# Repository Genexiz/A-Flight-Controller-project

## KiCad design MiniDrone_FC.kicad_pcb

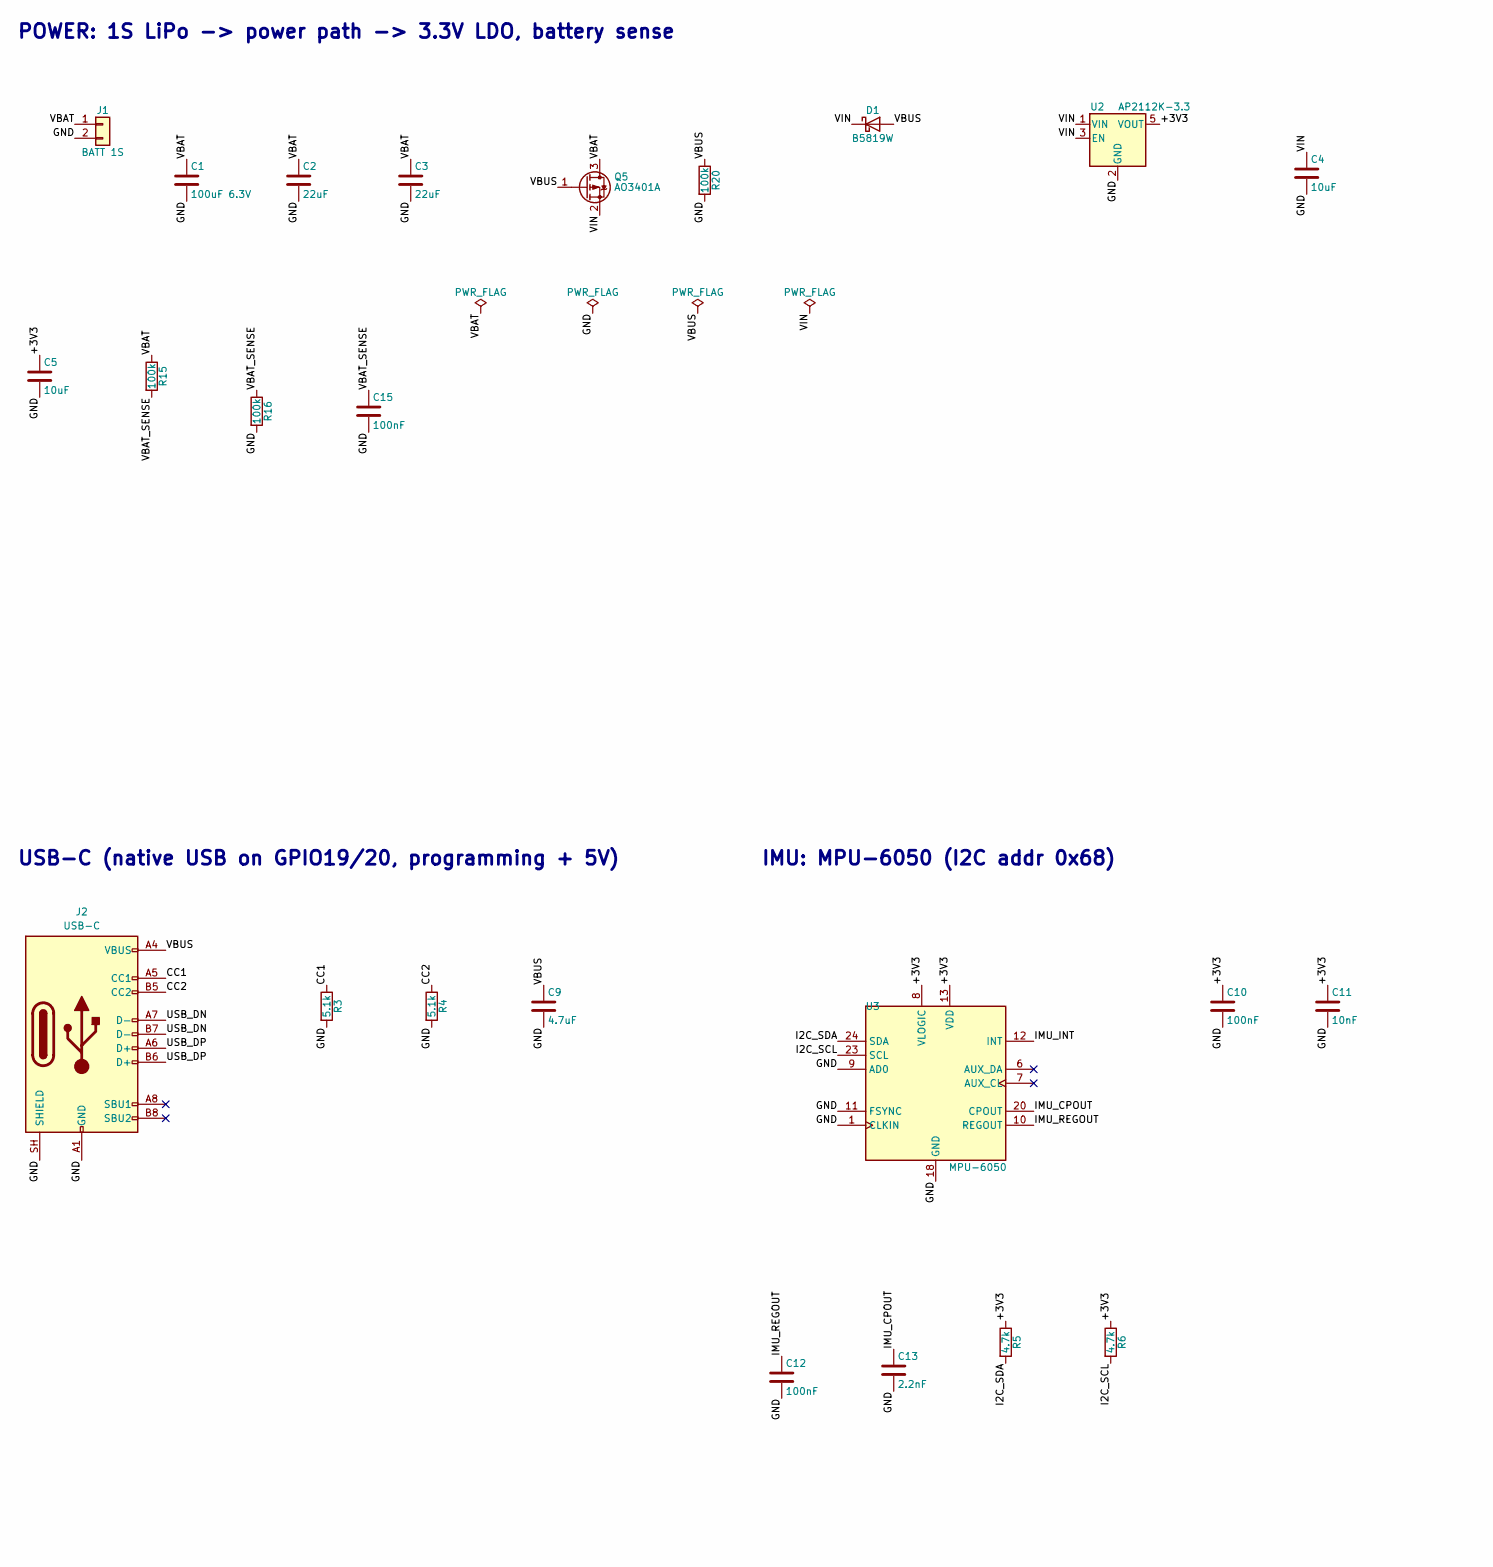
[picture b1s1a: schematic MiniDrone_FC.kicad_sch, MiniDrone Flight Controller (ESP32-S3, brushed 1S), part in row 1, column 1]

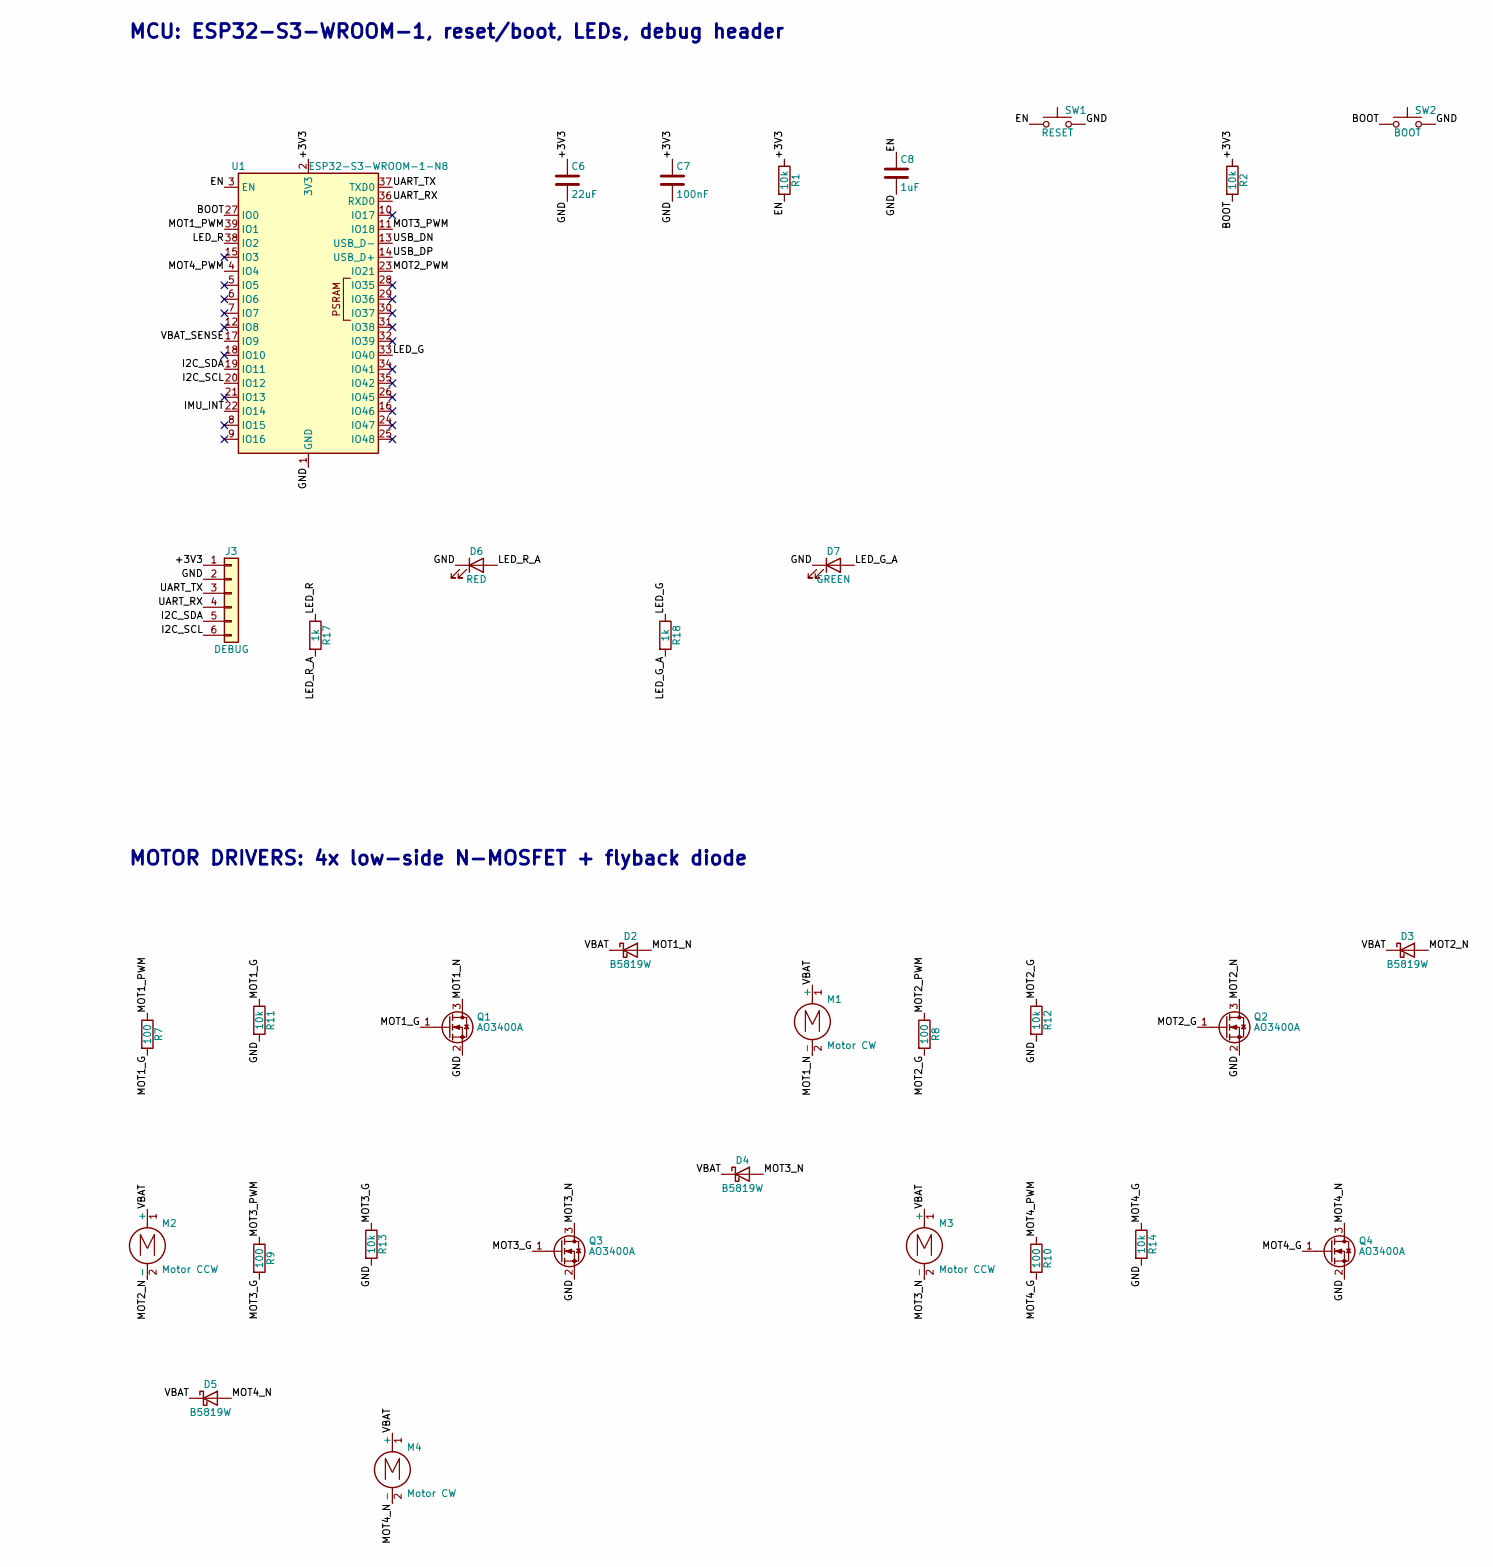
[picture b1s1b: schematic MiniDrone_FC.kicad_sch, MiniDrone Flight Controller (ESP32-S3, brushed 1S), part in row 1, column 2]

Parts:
C1: 100uF 6.3V; C_1206_3216Metric_Pad1.33x1.80mm_HandSolder; MPN GRM31CR60J107ME39
C2, C3, C6: 22uF; C_0805_2012Metric_Pad1.18x1.45mm_HandSolder
C4, C5: 10uF; C_0805_2012Metric_Pad1.18x1.45mm_HandSolder
C7, C10, C12, C15: 100nF; C_0805_2012Metric_Pad1.18x1.45mm_HandSolder
C8: 1uF; C_0805_2012Metric_Pad1.18x1.45mm_HandSolder
C9: 4.7uF; C_0805_2012Metric_Pad1.18x1.45mm_HandSolder
C11: 10nF; C_0805_2012Metric_Pad1.18x1.45mm_HandSolder
C13: 2.2nF; C_0805_2012Metric_Pad1.18x1.45mm_HandSolder
D1, D2, D3, D4, D5: B5819W; D_SOD-123; MPN B5819W
D6: RED; LED_0805_2012Metric_Pad1.15x1.40mm_HandSolder
D7: GREEN; LED_0805_2012Metric_Pad1.15x1.40mm_HandSolder
J1: BATT 1S; JST_PH_S2B-PH-SM4-TB_1x02-1MP_P2.00mm_Horizontal; MPN S2B-PH-SM4-TB
J2: USB-C; USB_C_Receptacle_HRO_TYPE-C-31-M-12; MPN TYPE-C-31-M-12
J3: DEBUG; PinHeader_1x06_P1.27mm_Vertical
M1, M4: Motor CW; SolderWire-0.15sqmm_1x02_P4mm_D0.5mm_OD1.5mm
M2, M3: Motor CCW; SolderWire-0.15sqmm_1x02_P4mm_D0.5mm_OD1.5mm
Q1, Q2, Q3, Q4: AO3400A; SOT-23; MPN AO3400A
Q5: AO3401A; SOT-23; MPN AO3401A
R1, R2, R11, R12, R13, R14: 10k; R_0805_2012Metric_Pad1.20x1.40mm_HandSolder
R3, R4: 5.1k; R_0805_2012Metric_Pad1.20x1.40mm_HandSolder
R5, R6: 4.7k; R_0805_2012Metric_Pad1.20x1.40mm_HandSolder
R7, R8, R9, R10: 100; R_0805_2012Metric_Pad1.20x1.40mm_HandSolder
R15, R16, R20: 100k; R_0805_2012Metric_Pad1.20x1.40mm_HandSolder
R17, R18: 1k; R_0805_2012Metric_Pad1.20x1.40mm_HandSolder
SW1: RESET; SW_SPST_PTS810; MPN PTS810SJM250SMTRLFS
SW2: BOOT; SW_SPST_PTS810; MPN PTS810SJM250SMTRLFS
U1: ESP32-S3-WROOM-1-N8; ESP32-S3-WROOM-1; MPN ESP32-S3-WROOM-1-N8
U2: AP2112K-3.3; SOT-23-5; MPN AP2112K-3.3TRG1
U3: MPU-6050; InvenSense_QFN-24_4x4mm_P0.5mm; MPN MPU-6050

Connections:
/+3V3: C5.1, C6.1, C7.1, C10.1, C11.1, J3.1, R1.1, R2.1, R5.1, R6.1, U1.2 (3V3), U2.5 (VOUT), U3.8 (VLOGIC), U3.13 (VDD)
/BOOT: R2.2, SW2.1, U1.27 (IO0)
/CC1: J2.A5 (CC1), R3.1
/CC2: J2.B5 (CC2), R4.1
/EN: C8.1, R1.2, SW1.1, U1.3 (EN)
/GND: C1.2, C2.2, C3.2, C4.2, C5.2, C6.2, C7.2, C8.2, C9.2, C10.2, C11.2, C12.2, C13.2, C15.2, D6.1 (K), D7.1 (K), J1.2, J2.A1 (GND), J2.A12 (GND), J2.B1 (GND), J2.B12 (GND), J2.SH (SHIELD), J3.2, Q1.2 (S), Q2.2 (S), Q3.2 (S), Q4.2 (S), R3.2, R4.2, R11.2, R12.2, R13.2, R14.2, R16.2, R20.2, SW1.2, SW2.2, U1.1 (GND), U1.40 (GND), U1.41 (GND), U2.2 (GND), U3.1 (CLKIN), U3.9 (AD0), U3.11 (FSYNC), U3.18 (GND)
/I2C_SCL: J3.6, R6.2, U1.20 (IO12), U3.23 (SCL)
/I2C_SDA: J3.5, R5.2, U1.19 (IO11), U3.24 (SDA)
/IMU_CPOUT: C13.1, U3.20 (CPOUT)
/IMU_INT: U1.22 (IO14), U3.12 (INT)
/IMU_REGOUT: C12.1, U3.10 (REGOUT)
/LED_G: R18.1, U1.33 (IO40)
/LED_G_A: D7.2 (A), R18.2
/LED_R: R17.1, U1.38 (IO2)
/LED_R_A: D6.2 (A), R17.2
/MOT1_G: Q1.1 (G), R7.2, R11.1
/MOT1_N: D2.2 (A), M1.2 (-), Q1.3 (D)
/MOT1_PWM: R7.1, U1.39 (IO1)
/MOT2_G: Q2.1 (G), R8.2, R12.1
/MOT2_N: D3.2 (A), M2.2 (-), Q2.3 (D)
/MOT2_PWM: R8.1, U1.23 (IO21)
/MOT3_G: Q3.1 (G), R9.2, R13.1
/MOT3_N: D4.2 (A), M3.2 (-), Q3.3 (D)
/MOT3_PWM: R9.1, U1.11 (IO18)
/MOT4_G: Q4.1 (G), R10.2, R14.1
/MOT4_N: D5.2 (A), M4.2 (-), Q4.3 (D)
/MOT4_PWM: R10.1, U1.4 (IO4)
/UART_RX: J3.4, U1.36 (RXD0)
/UART_TX: J3.3, U1.37 (TXD0)
/USB_DN: J2.A7 (D-), J2.B7 (D-), U1.13 (USB_D-)
/USB_DP: J2.A6 (D+), J2.B6 (D+), U1.14 (USB_D+)
/VBAT: C1.1, C2.1, C3.1, D2.1 (K), D3.1 (K), D4.1 (K), D5.1 (K), J1.1, M1.1 (+), M2.1 (+), M3.1 (+), M4.1 (+), Q5.3 (D), R15.1
/VBAT_SENSE: C15.1, R15.2, R16.1, U1.17 (IO9)
/VBUS: C9.1, D1.2 (A), J2.A4 (VBUS), J2.A9 (VBUS), J2.B4 (VBUS), J2.B9 (VBUS), Q5.1 (G), R20.1
/VIN: C4.1, D1.1 (K), Q5.2 (S), U2.1 (VIN), U2.3 (EN)

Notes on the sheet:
POWER: 1S LiPo -> power path -> 3.3V LDO, battery sense
MCU: ESP32-S3-WROOM-1, reset/boot, LEDs, debug header
USB-C (native USB on GPIO19/20, programming + 5V)
IMU: MPU-6050 (I2C addr 0x68)
MOTOR DRIVERS: 4x low-side N-MOSFET + flyback diode

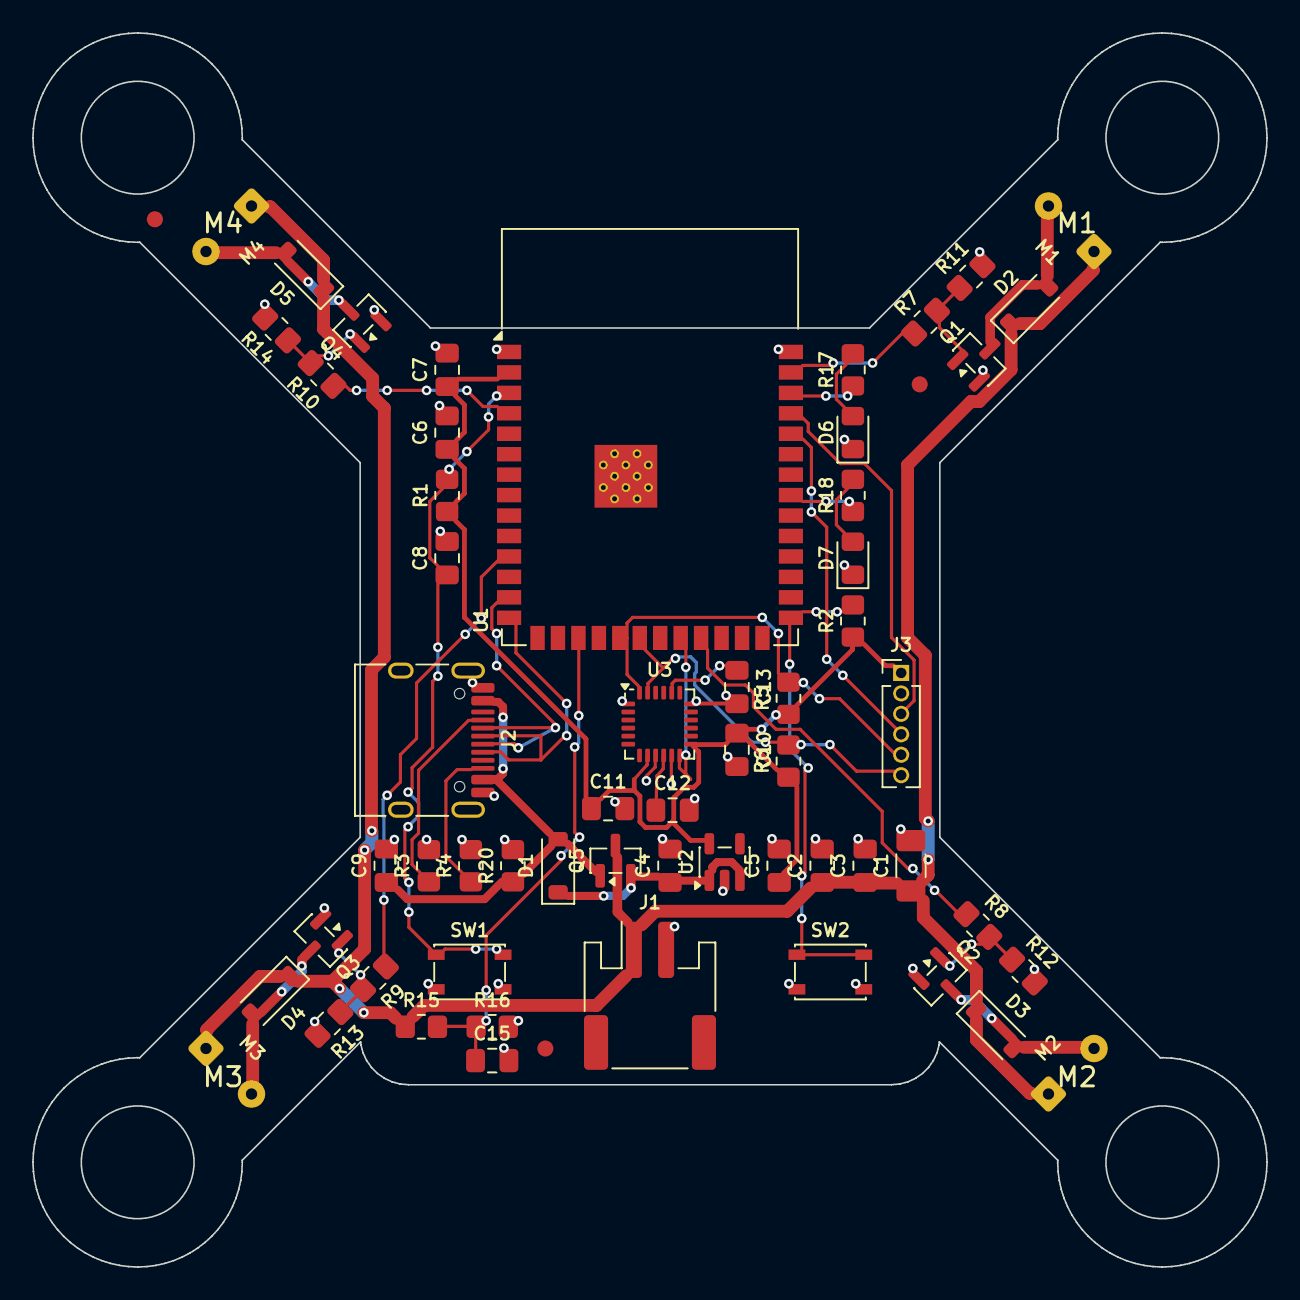
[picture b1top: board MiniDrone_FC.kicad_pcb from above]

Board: 2 copper layers, 76.6 x 76.6 mm, 60 parts (0 on the bottom side), 35 nets.

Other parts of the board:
FID1, FID2, FID3: Fiducial_1mm_Mask2mm
